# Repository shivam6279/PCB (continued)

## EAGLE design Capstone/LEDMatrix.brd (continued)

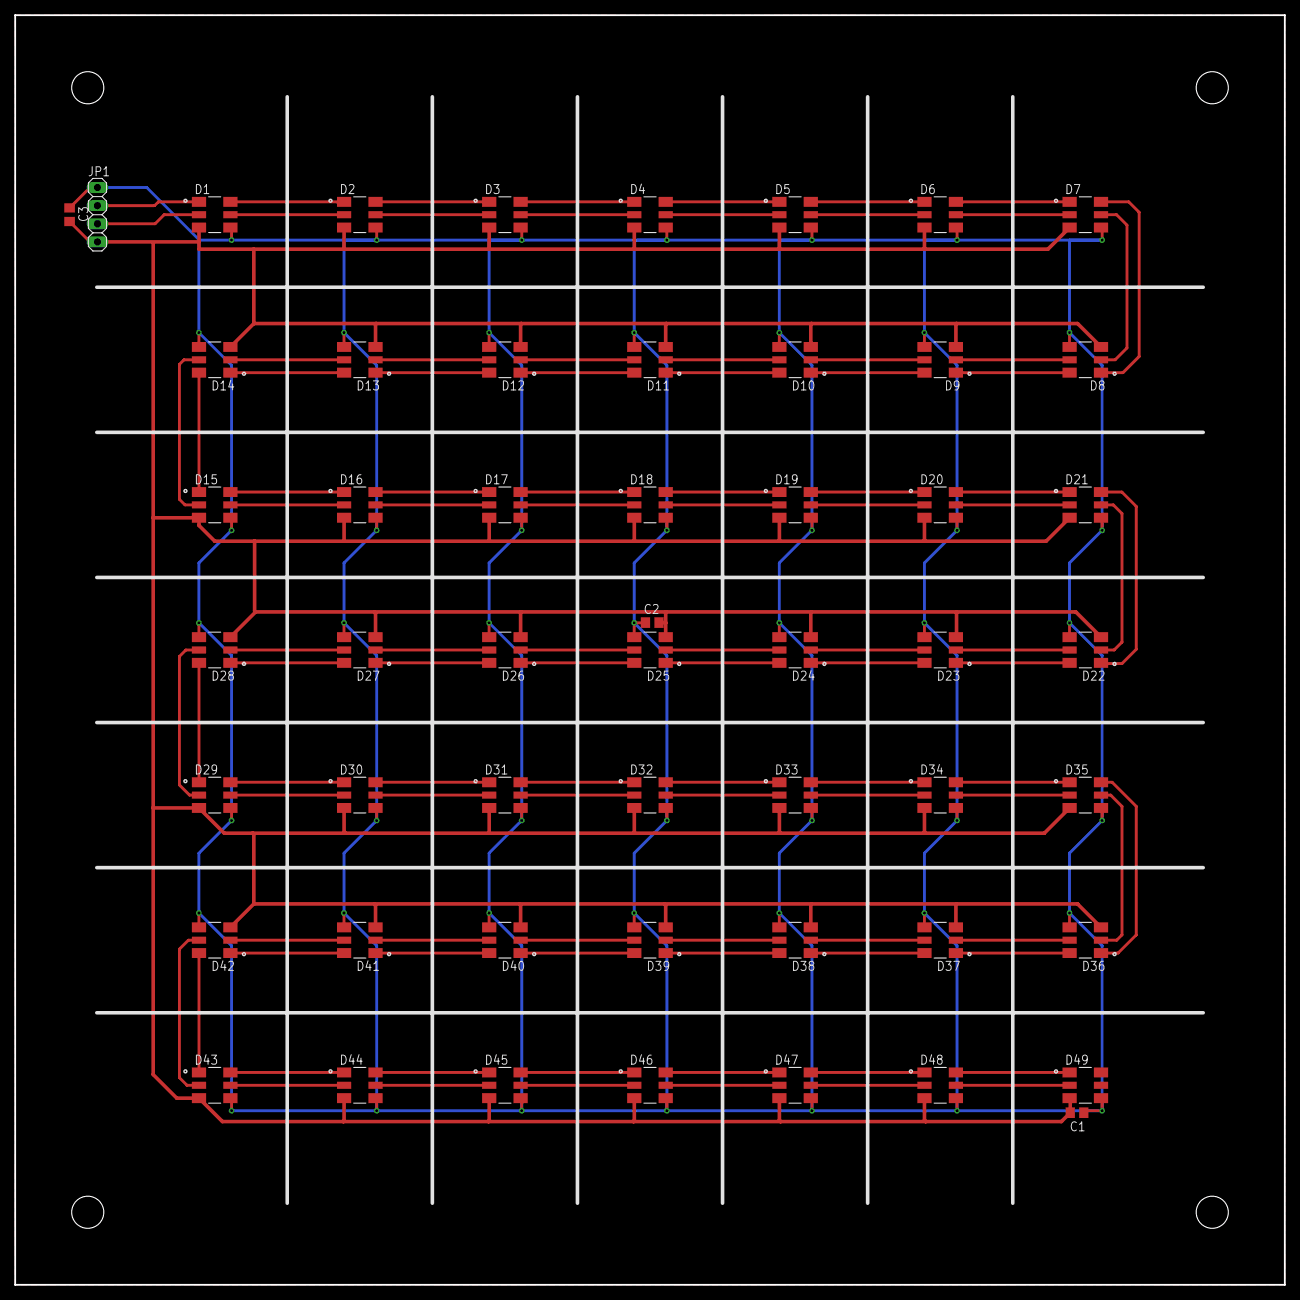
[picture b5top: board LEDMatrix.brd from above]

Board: 2 copper layers, 177.8 x 177.8 mm, 53 parts (0 on the bottom side), 100 nets.

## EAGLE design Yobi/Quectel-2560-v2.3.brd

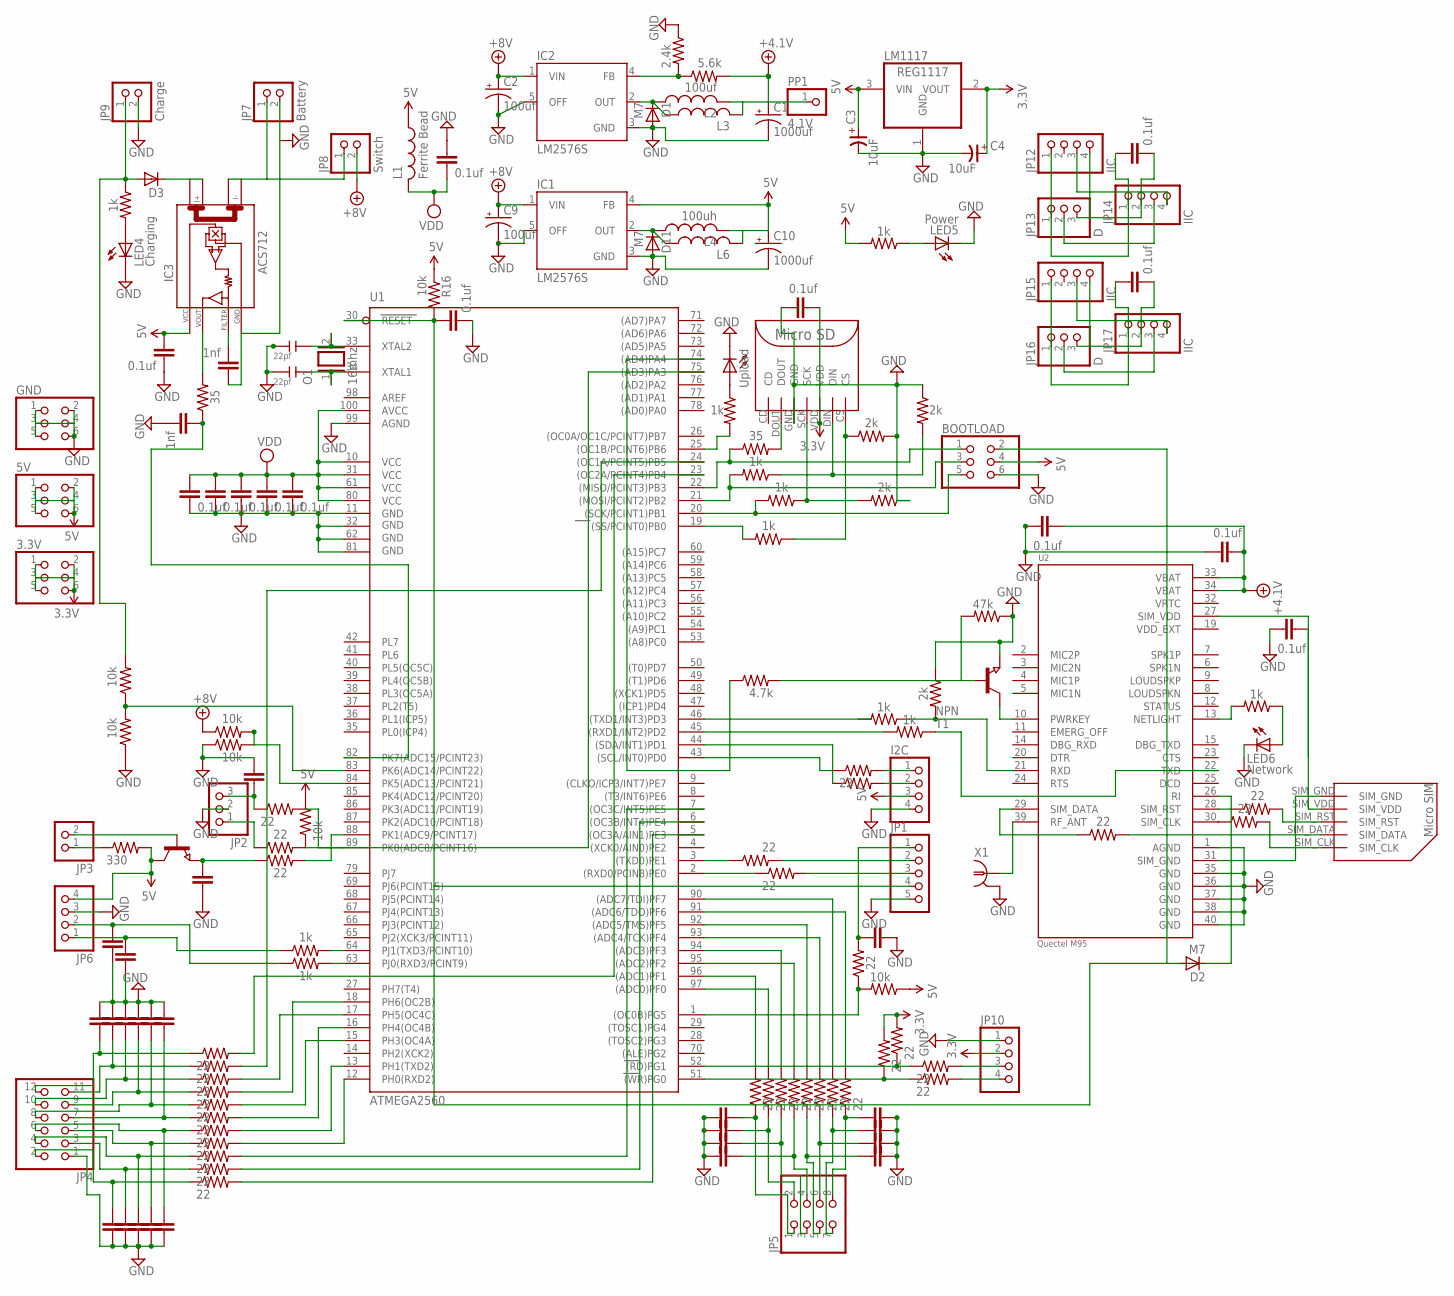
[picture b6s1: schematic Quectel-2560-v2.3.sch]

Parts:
3.3V, 5V: PINHD-2X3; 2X03
BOOTLOAD: PINHD-2X3; 2X03
C1, C10: 1000uf; 153CLV-1012
C2, C9: 100uf; CT7343
C3, C4: 10uF; 3528/T
C7, C8: 22pf; C0805
D1, D2, D11: M7; SOD106A
D3: BYS10; SOD106A
DC1, DC2, DC3, DC4, DC5, DC6, DC7, DC8, DC9, DC10, DC11, DC15, DC18, DC19: 0.1uf; C0805
DC12, DC13, DC14, DC16, DC17, DC20, DC21, DC22, DC23, DC24, DC25, DC26, DC27, DC28, DC29, DC30, DC31, DC32, DC33, DC34, DC35, DC36, DC37, DC38, DC39, DC40: 1nf; C0805
GND: PINHD-2X3; 2X03
I2C: PINHD-1X4; 1X04
IC1, IC2: LM2576S; TO263-5
IC3: ACS712; SO08
JP1: PINHD-1X5; 1X05
JP2: PINHD-1X3; 1X03
JP3: PINHD-1X2; 1X02
JP4: PINHD-2X6; 2X06
JP5: PINHD-2X4; 2X04
JP6, JP10: PINHD-1X4; 1X04
JP7: Battery; 1X02
JP8: Switch; 1X02
JP9: Charge; 1X02
JP12, JP14, JP15, JP17: IIC; 1X04
JP13, JP16: D; 1X03
L1: Ferrite Bead; L2012C
L2: 100uf; PIS2816
L3, L6: L-US6000-XXX-RC; 6000-XXXX-RC
L4: 100uh; PIS2816
LED2: Upload; CHIP-LED0805
LED4: Charging; CHIP-LED0805
LED5: Power; CHIP-LED0805
LED6: Network; CHIP-LED0805
LM1117: REG1117; SOT223
O1: 16mhz; QS
PP1: 4.1V; 1X01
R1, R35: 35; 0805
R2: 47k; 0805
R3: 4.7k; 0805
R4, R5, R12, R13, R19, R20, R21, R22, R27, R28, R30, R31, R32, R33, R34, R36, R37, R38, R39, R40, R41, R42, R48, R49, R51, R53, R54, R60, R61, R62, R63: 22; R0805
R6, R7, R8, R14, R15, R17, R18, R25, R26: 1k; 0805
R9, R23, R24, R29: 2k; 0805
R10, R11, R47: 22; 0805
R16, R43, R44, R56, R57: 10k; 0805
R45: 2.4k; 0805
R46: 5.6k; 0805
R50, R55: 10k; R0805
R52: 330; R0805
R58, R59: 1k; R0805
T1, T2: NPN; SOT23
U1: ATMEGA2560; TQFP100
U2: Quectel M95; XCVR_M95
U$1: MICROSD
U$2: MICROSIM
X1: LTI-SASF54GT

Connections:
3.3V: 3.3V.1, 3.3V.2, 3.3V.3, 3.3V.4, 3.3V.5, 3.3V.6, C4.+, DC10.2, JP10.2, LM1117.2 (VOUT), R62.2, R63.2, U$1.VDD
5V: 5V.1, 5V.2, 5V.3, 5V.4, 5V.5, 5V.6, BOOTLOAD.4, C3.+, C10.+, DC19.2, I2C.3, IC1.4 (FB), IC3.8 (VCC), JP6.4, L1.1, L4.2, L6.2, LM1117.3 (VIN), R16.1, R18.2, R50.1, R52.2, R55.2, T2.3 (C)
+4.1V: C1.+, DC6.2, DC7.2, L2.2, L3.2, PP1.1, R46.2, U2.33 (VBAT), U2.34 (VBAT)
+8V: C2.+, C9.+, IC1.1 (VIN), IC2.1 (VIN), JP8.2, R43.1
GND: BOOTLOAD.6, C1.-, C2.-, C3.-, C4.-, C7.1, C8.1, C9.-, C10.-, D1.A, D11.A, DC1.2, DC2.2, DC3.2, DC4.2, DC5.2, DC6.1, DC7.1, DC10.1, DC11.2, DC12.1, DC13.1, DC14.1, DC15.1, DC16.1, DC17.1, DC18.1, DC19.1, DC20.1, DC21.2, DC22.1, DC23.2, DC24.2, DC25.2, DC26.2, DC27.2, DC28.2, DC29.2, DC30.2, DC31.2, DC32.2, DC33.1, DC34.1, DC35.1, DC36.1, DC37.2, DC38.2, DC39.1, DC40.2, GND.1, GND.2, GND.3, GND.4, GND.5, GND.6, I2C.4, IC1.3 (GND), IC1.5 (OFF), IC2.3 (GND), IC2.5 (OFF), IC3.5 (GND), JP1.5, JP2.2, JP4.1, JP6.3, JP7.2, JP9.2, JP10.1, LED2.C, LED4.C, LED5.C, LED6.C, LM1117.1 (GND), R2.1, R9.1, R23.2, R24.1, R29.1, R44.1, R45.1, R57.1, T1.2 (E), U1.11 (GND), U1.32 (GND1), U1.62 (GND2), U1.81 (GND3), U1.99 (AGND), U2.1 (AGND), U2.35 (GND), U2.36 (GND), U2.37 (GND), U2.38 (GND), U2.40 (GND), U$1.GND, X1.2, X1.3 (2), X1.4 (2), X1.5 (2)
unnamed: U2.31 (SIM_GND), U$2.SIM_GND
unnamed: DC15.2, U2.27 (SIM_VDD), U$2.SIM_VDD
unnamed: R10.1, U2.28 (SIM_RST)
unnamed: R11.1, U2.30 (SIM_CLK)
unnamed: DC8.1, JP12.1, JP13.1, JP14.1
unnamed: R10.2, U$2.SIM_RST
unnamed: LED2.A, R25.1
unnamed: R33.1, R50.2, U1.1 ((OC0B)PG5)
unnamed: R32.2, U1.5 ((OC3A/AIN1)PE3)
unnamed: R7.1, R24.2, U$1.SCK
unnamed: R31.2, U1.6 ((OC3B/INT4)PE4)
unnamed: R6.1, R9.2, U$1.DIN
unnamed: BOOTLOAD.2, D2.A, DC11.1, JP1.4, R16.2, U1.30 (RESET)
unnamed: DC8.2, JP12.4, JP13.3, JP14.2
unnamed: JP13.2, JP14.3
unnamed: BOOTLOAD.3, R6.2, U1.21 ((MOSI/PCINT2)PB2)
unnamed: BOOTLOAD.5, R7.2, U1.20 ((SCK/PCINT1)PB1)
unnamed: DC21.1, R1.1, U1.82 (PK7(ADC15/PCINT23))
unnamed: IC3.4 (I-_1), JP7.1, JP8.1
unnamed: R8.2, U1.19 ((SS/PCINT0)PB0)
unnamed: U2.39 (RF_ANT), X1.1
unnamed: R13.2, U1.18 (PH6(OC2B))
unnamed: R22.2, U1.12 (PH0(RXD2))
unnamed: D3.A, JP9.1, R26.1, R56.2
unnamed: R27.2, U1.96 ((ADC1)PF1)
unnamed: LED4.A, R26.2
unnamed: IC3.7 (VOUT), R1.2
unnamed: R11.2, U$2.SIM_CLK
unnamed: C7.2, O1.2, U1.33 (XTAL2)
unnamed: C8.2, O1.1, U1.34 (XTAL1)
unnamed: R21.2, U1.13 (PH1(TXD2))
unnamed: R28.2, U1.97 ((ADC0)PF0)
unnamed: R34.2, U1.94 ((ADC3)PF3)
unnamed: R8.1, R23.1, U$1.CS
unnamed: R19.2, U1.15 (PH3(OC4A))
unnamed: R20.2, U1.16 (PH4(OC4B))
unnamed: R12.2, U1.17 (PH5(OC4C))
unnamed: R25.2, U1.25 ((OC1B/PCINT6)PB6)
unnamed: R14.2, U1.46 ((TXD1/INT3)PD3)
unnamed: R15.2, U1.45 ((RXD1/INT2)PD2)
unnamed: R14.1, R29.2, U2.21 (RXD)
unnamed: R15.1, U2.22 (TXD)
unnamed: DC29.1, JP5.8, R40.1
unnamed: R4.2, U1.23 ((OC2A/PCINT4)PB4)
unnamed: JP12.3, JP14.4
unnamed: R5.2, U1.24 ((OC1A/PCINT5)PB5)
unnamed: R36.2, U1.95 ((ADC2)PF2)
unnamed: BOOTLOAD.1, R35.1, U1.22 ((MISO/PCINT3)PB3)
unnamed: R17.2, U2.13 (NETLIGHT)
unnamed: LED6.A, R17.1
unnamed: R41.1, U1.3 ((TXD0)PE1)
unnamed: R42.1, U1.2 ((RXD0/PCIN8)PE0)
unnamed: DC13.2, JP4.11, R5.1
unnamed: DC23.1, JP1.1, R33.2
unnamed: DC25.1, JP4.3, R31.1
unnamed: DC27.1, JP4.5, R22.1
unnamed: DC22.2, JP4.7, R20.1
unnamed: LED5.A, R18.1
unnamed: DC16.2, JP4.9, R13.1
unnamed: DC24.1, JP4.2, R32.1
unnamed: JP1.2, R41.2
unnamed: R35.2, U$1.DOUT
unnamed: D11.K, IC1.2 (OUT), L4.1, L6.1
unnamed: DC28.1, JP4.6, R21.1
unnamed: R47.2, U$2.SIM_DATA
unnamed: R47.1, U2.29 (SIM_DATA)
unnamed: DC17.2, JP4.8, R19.1
unnamed: DC14.2, JP4.10, R12.1
unnamed: DC12.2, JP4.12, R4.1
unnamed: DC9.1, JP15.1, JP16.1, JP17.1
unnamed: DC26.1, JP4.4, R30.1
unnamed: JP1.3, R42.2
unnamed: R30.2, U1.7 ((OC3C/INT5)PE5)
unnamed: R43.2, R44.2, U1.84 (PK5(ADC13/PCINT21))
unnamed: D1.K, IC2.2 (OUT), L2.1, L3.1
unnamed: IC2.4 (FB), R45.2, R46.1
unnamed: DC39.2, JP2.3, R51.1
unnamed: I2C.1, R49.2
unnamed: I2C.2, R48.2
unnamed: DC9.2, JP15.4, JP16.3, JP17.2
unnamed: JP15.3, JP17.4
unnamed: JP16.2, JP17.3
unnamed: T1.3 (C), U2.10 (PWRKEY)
unnamed: R2.2, R3.2, T1.1 (B)
unnamed: R3.1, U1.74 ((AD4)PA4)
unnamed: D2.K, U2.26 (RI)
unnamed: DC31.1, JP5.6, R37.1
unnamed: D3.K, IC3.1 (I+_0)
unnamed: DC20.2, IC3.6 (FILTER)
unnamed: DC36.2, JP5.4, R36.1
unnamed: DC34.2, JP5.2, R28.1
unnamed: R48.1, U1.44 ((SDA/INT1)PD1)
unnamed: R49.1, U1.43 ((SCL/INT0)PD0)
unnamed: DC30.1, JP5.7, R39.1
unnamed: DC32.1, JP5.5, R38.1
unnamed: DC35.2, JP5.3, R34.1
unnamed: DC33.2, JP5.1, R27.1
unnamed: R38.2, U1.92 ((ADC5/TMS)PF5)
unnamed: R37.2, U1.93 ((ADC4/TCK)PF4)
unnamed: R39.2, U1.90 ((ADC7/TDI)PF7)
unnamed: R40.2, U1.91 ((ADC6/TDO)PF6)
unnamed: JP2.1, R54.1
unnamed: JP3.1, R52.1
unnamed: JP3.2, T2.1 (B)
unnamed: DC40.1, R53.1, T2.2 (E)
unnamed: R54.2, R55.1, U1.75 ((AD3)PA3)
unnamed: R51.2, U1.89 (PK0(ADC8/PCINT16))
unnamed: R53.2, U1.88 (PK1(ADC9/PCINT17))
unnamed: R60.1, R62.1, U1.51 ((WR)PG0)
unnamed: R56.1, R57.2, U1.83 (PK6(ADC14/PCINT22))
unnamed: R58.2, U1.64 (PJ1(TXD3/PCINT10))
unnamed: R59.2, U1.63 (PJ0(RXD3/PCINT9))
unnamed: DC38.1, JP6.1, R58.1
unnamed: DC37.1, JP6.2, R59.1
unnamed: R61.1, R63.1, U1.52 ((RD)PG1)
unnamed: JP10.4, R60.2
unnamed: JP10.3, R61.2
VDD: DC1.1, DC2.1, DC3.1, DC4.1, DC5.1, DC18.2, L1.2, U1.10 (VCC), U1.31 (VCC1), U1.61 (VCC2), U1.80 (VCC3), U1.100 (AVCC)
VDD_EXT: U2.19 (VDD_EXT)
VRTC: U2.32 (VRTC)

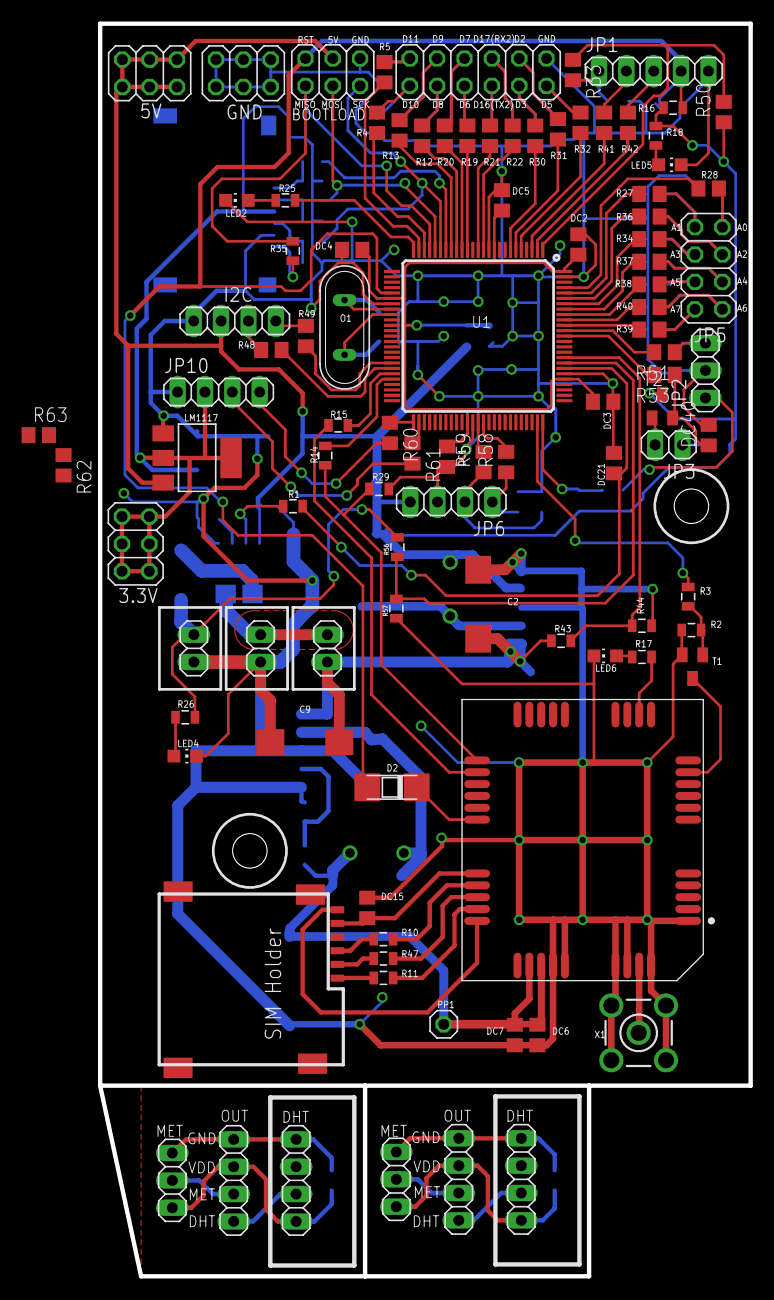
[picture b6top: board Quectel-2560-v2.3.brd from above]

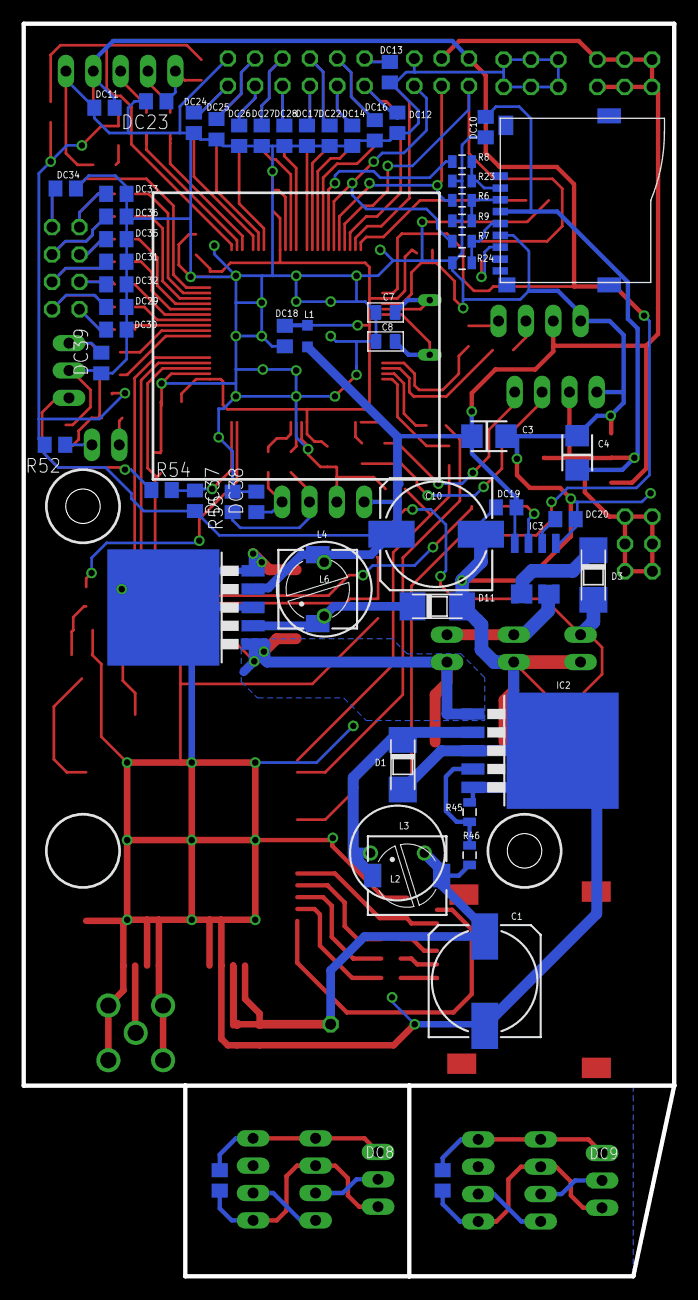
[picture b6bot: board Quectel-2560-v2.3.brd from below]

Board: 2 copper layers, 60.4 x 116.3 mm, 158 parts (59 on the bottom side), 123 nets.

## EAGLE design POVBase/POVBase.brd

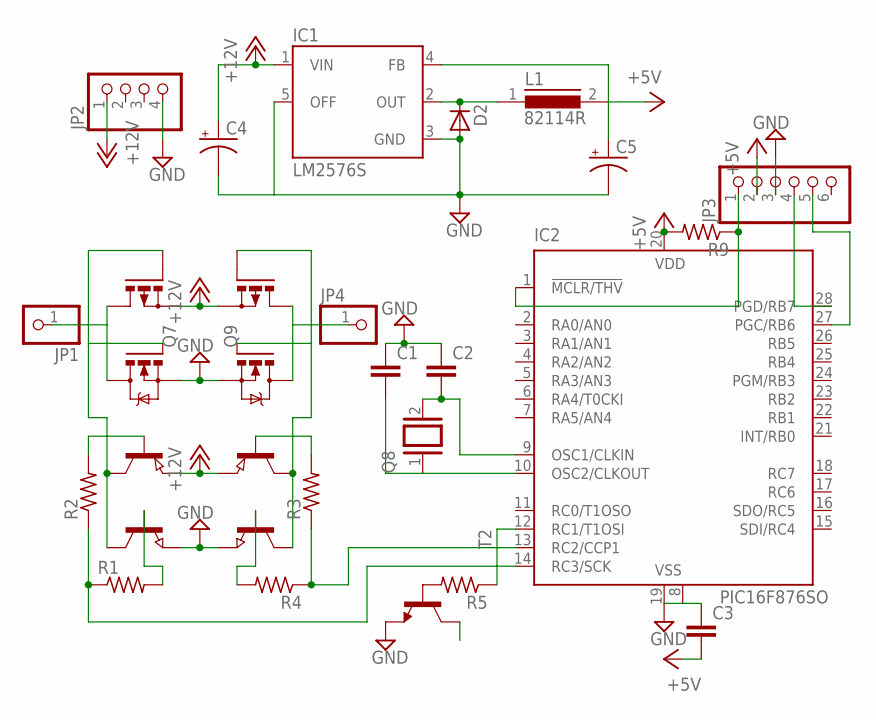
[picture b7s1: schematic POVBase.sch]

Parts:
C1, C2, C3: C-EUC0805; C0805
C4: CPOL-USE2.5-7; E2,5-7
C5: CPOL-USE1.8-4; E1,8-4
D2: DIODE_E-SMC; DIODE_SMC
IC1: LM2576S; TO263-5
IC2: PIC16F876SO; SO28W
JP1, JP4: PINHD-1X1; 1X01
JP2: PINHD-1X4; 1X04
JP3: PINHD-1X6; 1X06
L1: 82114R
Q1, Q2: NPN-TRANSISTOR_SOT23; SOT23
Q3, Q4: PNP-TRANSISTOR_SOT23; SOT23
Q5, Q6: IRF540; TO220BV
Q7, Q9: PMOSFET_PTO220BV; TO220BV
Q8: XTAL/S; QS
R1, R2, R3, R4, R5, R9: R-US_R0805; R0805
T2: 2SC1306; TO220BV

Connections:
+5V: C3.2, C5.+, IC1.4 (FB), IC2.20 (VDD), JP3.2, L1.2, R9.2
+12V: C4.+, IC1.1 (VIN), JP2.1, Q3.2 (E), Q4.2 (E), Q7.S, Q9.S
GND: C1.1, C2.1, C3.1, C4.-, C5.-, D2.A (C), IC1.3 (GND), IC1.5 (OFF), IC2.8 (VSS), IC2.19 (VSS), JP2.4, JP3.3, Q1.2 (E), Q2.2 (E), Q5.S, Q6.S, T2.3 (E)
unnamed: Q1.3 (C), Q3.3 (C), Q5.G, Q7.G
unnamed: Q1.1 (B), R1.2
unnamed: Q2.1 (B), R4.2
unnamed: Q2.3 (C), Q4.3 (C), Q6.G, Q9.G
unnamed: Q3.1 (B), R2.2
unnamed: Q4.1 (B), R3.2
unnamed: IC2.14 (RC3/SCK), R1.1, R2.1
unnamed: IC2.13 (RC2/CCP1), R3.1, R4.1
unnamed: JP4.1, Q6.D, Q9.D
unnamed: JP1.1, Q5.D, Q7.D
unnamed: IC2.1 (!MCLR/THV), JP3.1, R9.1
unnamed: IC2.28 (PGD/RB7), JP3.4
unnamed: IC2.27 (PGC/RB6), JP3.5
unnamed: D2.C (A), IC1.2 (OUT), L1.1
unnamed: C1.2, IC2.10 (OSC2/CLKOUT), Q8.1
unnamed: C2.2, IC2.9 (OSC1/CLKIN), Q8.2
unnamed: IC2.12 (RC1/T1OSI), R5.1
unnamed: R5.2, T2.1 (B)

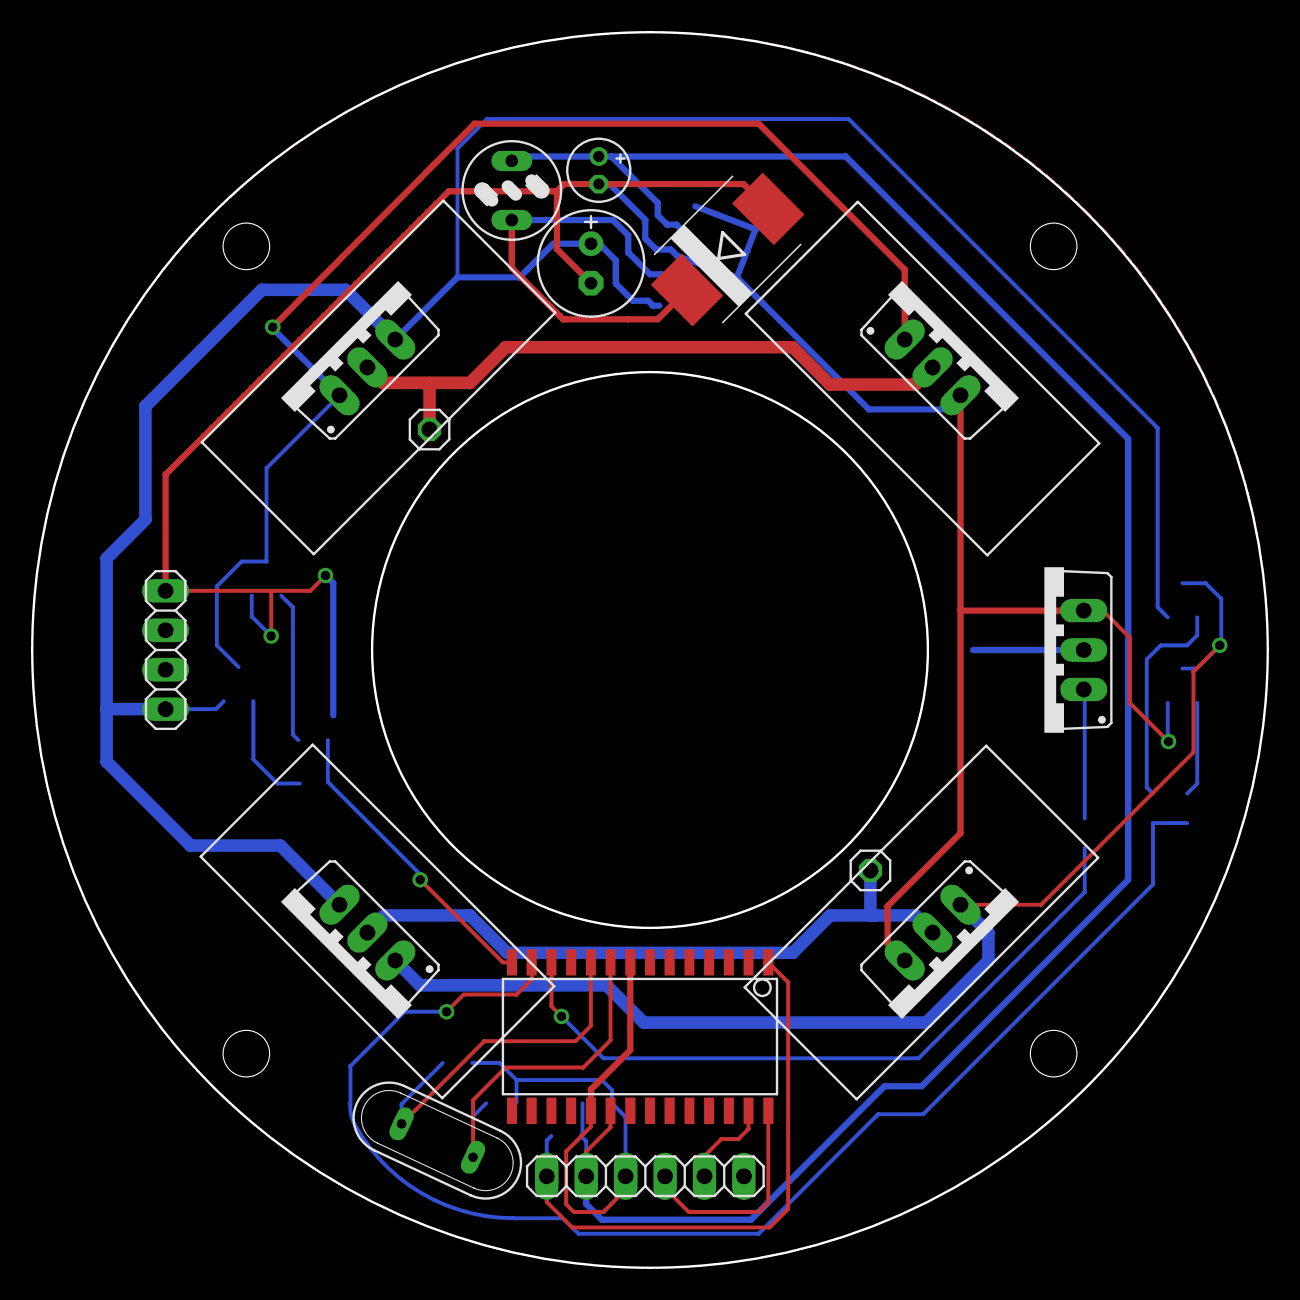
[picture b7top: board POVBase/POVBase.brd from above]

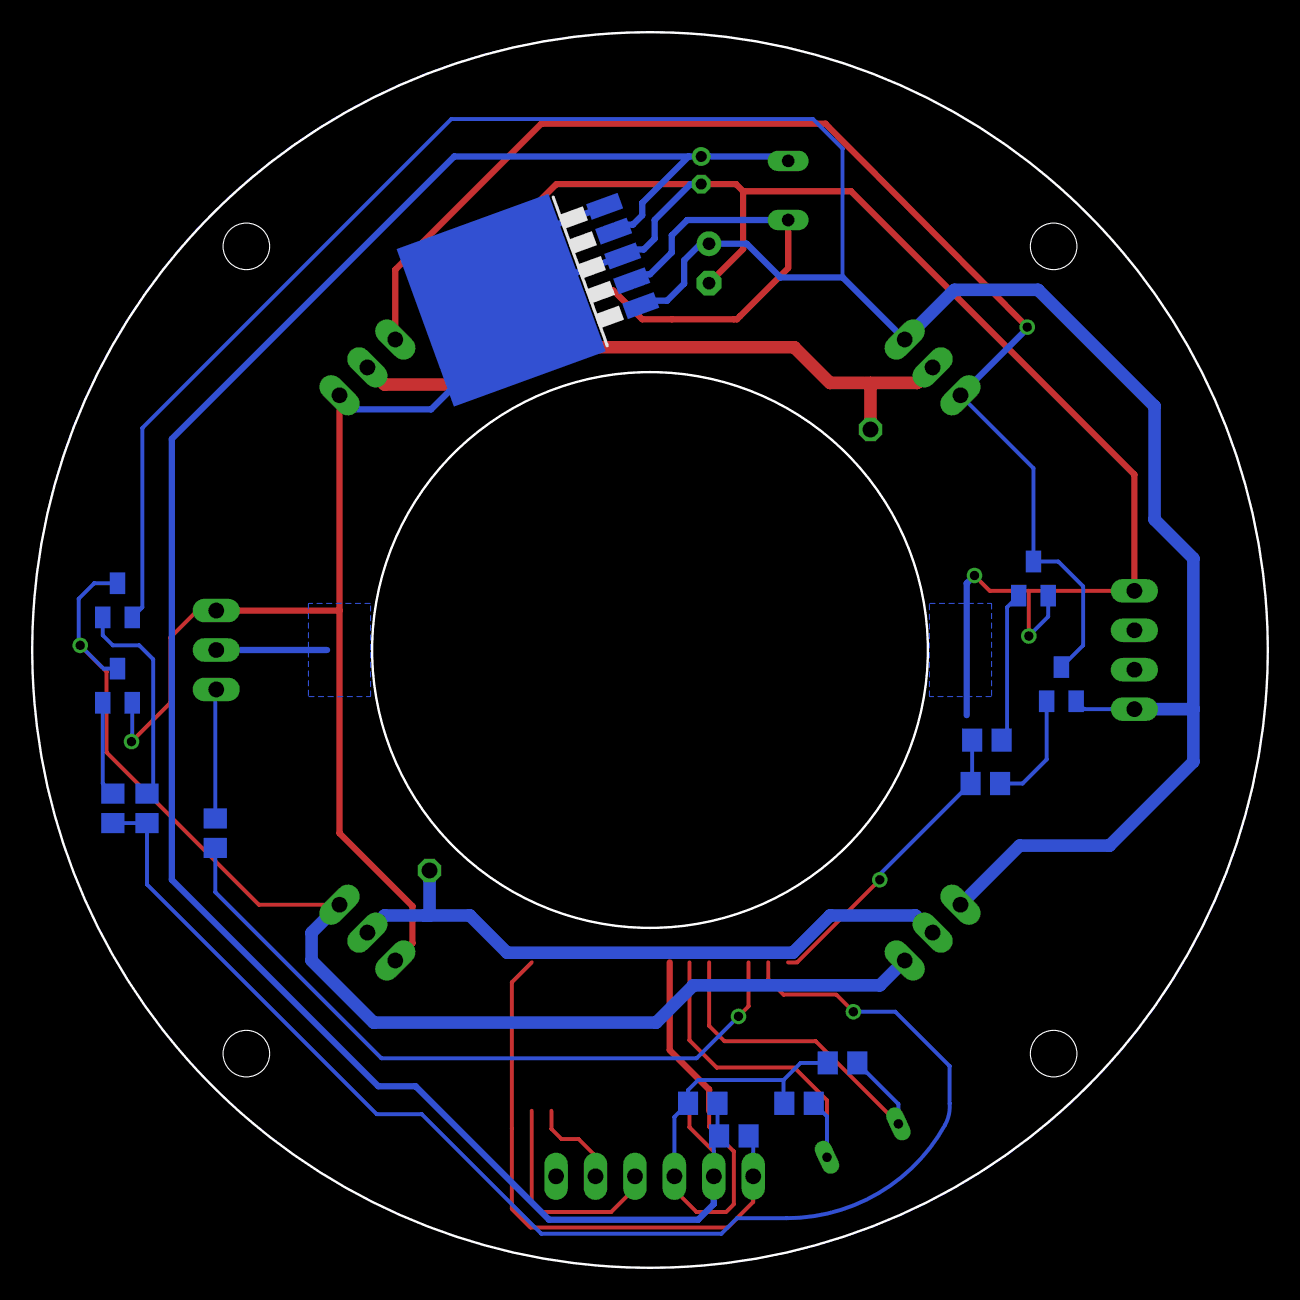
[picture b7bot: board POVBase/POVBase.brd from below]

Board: 2 copper layers, 79.6 x 79.6 mm, 29 parts (14 on the bottom side), 21 nets.

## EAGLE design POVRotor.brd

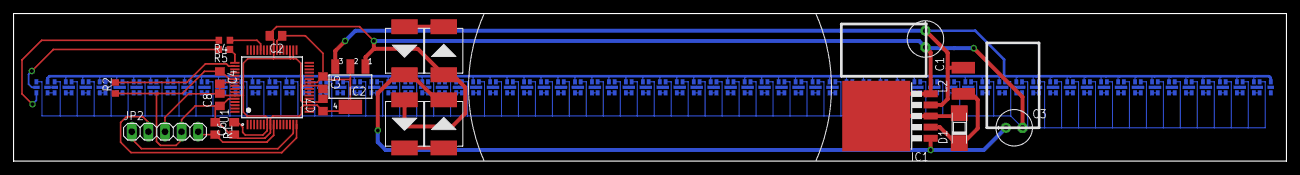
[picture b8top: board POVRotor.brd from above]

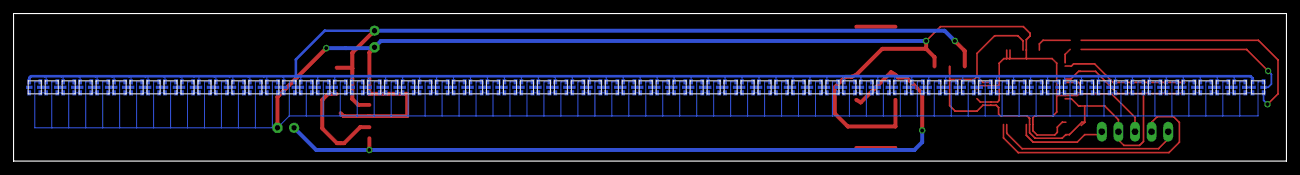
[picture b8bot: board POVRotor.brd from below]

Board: 2 copper layers, 195.0 x 22.6 mm, 95 parts (73 on the bottom side), 159 nets.

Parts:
C1, C3: E2,5-6E
C2, C4, C5, C6, C7, C8: C0805
D1: SOD106A
D2, D3, D4, D5: SMD-DIODE-SCHOTTKY-40V-3A(DO-214AB); DO-214AB
IC1: LM2576S; TO263-5
IC2: SOT223
JP2: 1X05
L2: L4532P
R1: R0805
R2, R4, R5: R0603
U1: PIC32MZ2048EFH064-I/PT; QFP50P1200X1200X120-64N
U$1, U$2, U$3, U$4, U$5, U$6, U$7, U$8, U$9, U$10, U$11, U$12, U$13, U$14, U$15, U$16, U$17, U$18, U$19, U$20, U$21, U$22, U$23, U$24, U$25, U$26, U$27, U$28, U$29, U$30, U$31, U$32, U$33, U$34, U$35, U$36, U$37, U$38, U$39, U$40, U$41, U$42, U$43, U$44, U$45, U$46, U$47, U$48, U$49, U$50, U$51, U$52, U$53, U$54, U$55, U$56, U$57, U$58, U$59, U$60, U$61, U$62, U$63, U$64, U$65, U$66, U$67, U$68, U$69, U$70, U$71, U$72, U$73: 2020LED

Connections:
+3V3: C2.1, C4.1, C5.1, C6.1, C7.1, C8.1, IC2.2, JP2.4, R1.1, R2.1, U1.8, U1.19, U1.26, U1.39, U1.54, U1.60
+5V: C1.+, IC1.4, IC2.3, L2.2, U$1.VCC, U$2.VCC, U$3.VCC, U$4.VCC, U$5.VCC, U$6.VCC, U$7.VCC, U$8.VCC, U$9.VCC, U$10.VCC, U$11.VCC, U$12.VCC, U$13.VCC, U$14.VCC, U$15.VCC, U$16.VCC, U$17.VCC, U$18.VCC, U$19.VCC, U$20.VCC, U$21.VCC, U$22.VCC, U$23.VCC, U$24.VCC, U$25.VCC, U$26.VCC, U$27.VCC, U$28.VCC, U$29.VCC, U$30.VCC, U$31.VCC, U$32.VCC, U$33.VCC, U$34.VCC, U$35.VCC, U$36.VCC, U$37.VCC, U$38.VCC, U$39.VCC, U$40.VCC, U$41.VCC, U$42.VCC, U$43.VCC, U$44.VCC, U$45.VCC, U$46.VCC, U$47.VCC, U$48.VCC, U$49.VCC, U$50.VCC, U$51.VCC, U$52.VCC, U$53.VCC, U$54.VCC, U$55.VCC, U$56.VCC, U$57.VCC, U$58.VCC, U$59.VCC, U$60.VCC, U$61.VCC, U$62.VCC, U$63.VCC, U$64.VCC, U$65.VCC, U$66.VCC, U$67.VCC, U$68.VCC, U$69.VCC, U$70.VCC, U$71.VCC, U$72.VCC, U$73.VCC
+15V: C3.+, D2.2, D3.2, IC1.1
GND: C1.-, C2.2, C3.-, C4.2, C5.2, C6.2, C7.2, C8.2, D1.A, D4.1, D5.1, IC1.3, IC1.5, IC2.1, JP2.3, U1.7, U1.20, U1.25, U1.34, U1.35, U1.40, U1.55, U1.59, U$1.GND, U$2.GND, U$3.GND, U$4.GND, U$5.GND, U$6.GND, U$7.GND, U$8.GND, U$9.GND, U$10.GND, U$11.GND, U$12.GND, U$13.GND, U$14.GND, U$15.GND, U$16.GND, U$17.GND, U$18.GND, U$19.GND, U$20.GND, U$21.GND, U$22.GND, U$23.GND, U$24.GND, U$25.GND, U$26.GND, U$27.GND, U$28.GND, U$29.GND, U$30.GND, U$31.GND, U$32.GND, U$33.GND, U$34.GND, U$35.GND, U$36.GND, U$37.GND, U$38.GND, U$39.GND, U$40.GND, U$41.GND, U$42.GND, U$43.GND, U$44.GND, U$45.GND, U$46.GND, U$47.GND, U$48.GND, U$49.GND, U$50.GND, U$51.GND, U$52.GND, U$53.GND, U$54.GND, U$55.GND, U$56.GND, U$57.GND, U$58.GND, U$59.GND, U$60.GND, U$61.GND, U$62.GND, U$63.GND, U$64.GND, U$65.GND, U$66.GND, U$67.GND, U$68.GND, U$69.GND, U$70.GND, U$71.GND, U$72.GND, U$73.GND
unnamed: D2.1, D5.2
unnamed: D3.1, D4.2
unnamed: D1.K, IC1.2, L2.1
unnamed: R2.2, U1.50
unnamed: U$1.SDI, U$2.SDO
unnamed: U$10.SDO, U$11.SDI
unnamed: U$10.CLKO, U$11.CLKI
unnamed: U$1.CLKI, U$2.CLKO
unnamed: U$11.SDO, U$12.SDI
unnamed: JP2.2, U1.16
unnamed: JP2.1, U1.15
unnamed: JP2.5, R1.2, U1.9
unnamed: R4.2, U$2.SDI
unnamed: U$1.SDO, U$3.SDI
unnamed: R5.2, U$2.CLKI
unnamed: R5.1, U1.49
unnamed: U$1.CLKO, U$3.CLKI
unnamed: R4.1, U1.44
unnamed: U$11.CLKO, U$12.CLKI
unnamed: U$12.SDO, U$13.SDI
unnamed: U$12.CLKO, U$13.CLKI
unnamed: U$13.SDO, U$14.SDI
unnamed: U$3.SDO, U$4.SDI
unnamed: U$3.CLKO, U$4.CLKI
unnamed: U$13.CLKO, U$14.CLKI
unnamed: U$14.SDO, U$15.SDI
unnamed: U$14.CLKO, U$15.CLKI
unnamed: U$4.SDO, U$5.SDI
unnamed: U$4.CLKO, U$5.CLKI
unnamed: U$15.SDO, U$16.SDI
unnamed: U$15.CLKO, U$16.CLKI
unnamed: U$16.SDO, U$17.SDI
unnamed: U$16.CLKO, U$17.CLKI
unnamed: U$5.SDO, U$6.SDI
unnamed: U$5.CLKO, U$6.CLKI
unnamed: U$17.SDO, U$18.SDI
unnamed: U$17.CLKO, U$18.CLKI
unnamed: U$18.SDO, U$19.SDI
unnamed: U$18.CLKO, U$19.CLKI
unnamed: U$6.SDO, U$7.SDI
unnamed: U$19.SDO, U$20.SDI
unnamed: U$19.CLKO, U$20.CLKI
unnamed: U$20.SDO, U$21.SDI
unnamed: U$20.CLKO, U$21.CLKI
unnamed: U$21.SDO, U$22.SDI
unnamed: U$6.CLKO, U$7.CLKI
unnamed: U$21.CLKO, U$22.CLKI
unnamed: U$22.SDO, U$23.SDI
unnamed: U$22.CLKO, U$23.CLKI
unnamed: U$23.SDO, U$24.SDI
unnamed: U$23.CLKO, U$24.CLKI
unnamed: U$7.SDO, U$8.SDI
unnamed: U$24.SDO, U$25.SDI
unnamed: U$7.CLKO, U$8.CLKI
unnamed: U$24.CLKO, U$25.CLKI
unnamed: U$25.SDO, U$26.SDI
unnamed: U$25.CLKO, U$26.CLKI
unnamed: U$8.SDO, U$9.SDI
unnamed: U$8.CLKO, U$9.CLKI
unnamed: U$26.SDO, U$27.SDI
unnamed: U$26.CLKO, U$27.CLKI
unnamed: U$9.SDO, U$10.SDI
unnamed: U$9.CLKO, U$10.CLKI
unnamed: U$27.SDO, U$28.SDI
unnamed: U$27.CLKO, U$28.CLKI
unnamed: U$28.SDO, U$29.SDI
unnamed: U$28.CLKO, U$29.CLKI
unnamed: U$29.SDO, U$30.SDI
unnamed: U$29.CLKO, U$30.CLKI
unnamed: U$30.SDO, U$31.SDI
unnamed: U$30.CLKO, U$31.CLKI
unnamed: U$31.SDO, U$32.SDI
unnamed: U$31.CLKO, U$32.CLKI
unnamed: U$32.SDO, U$33.SDI
unnamed: U$32.CLKO, U$33.CLKI
unnamed: U$33.SDO, U$34.SDI
unnamed: U$33.CLKO, U$34.CLKI
unnamed: U$34.SDO, U$35.SDI
unnamed: U$34.CLKO, U$35.CLKI
unnamed: U$35.SDO, U$36.SDI
unnamed: U$35.CLKO, U$36.CLKI
unnamed: U$36.SDO, U$37.SDI
unnamed: U$36.CLKO, U$37.CLKI
unnamed: U$37.SDO, U$38.SDI
unnamed: U$37.CLKO, U$38.CLKI
unnamed: U$38.SDO, U$39.SDI
unnamed: U$38.CLKO, U$39.CLKI
unnamed: U$39.SDO, U$40.SDI
unnamed: U$39.CLKO, U$40.CLKI
unnamed: U$40.SDO, U$41.SDI
unnamed: U$40.CLKO, U$41.CLKI
unnamed: U$41.SDO, U$42.SDI
unnamed: U$41.CLKO, U$42.CLKI
unnamed: U$42.SDO, U$43.SDI
unnamed: U$42.CLKO, U$43.CLKI
unnamed: U$43.SDO, U$44.SDI
unnamed: U$43.CLKO, U$44.CLKI
unnamed: U$44.SDO, U$45.SDI
unnamed: U$44.CLKO, U$45.CLKI
unnamed: U$45.SDO, U$46.SDI
unnamed: U$45.CLKO, U$46.CLKI
unnamed: U$46.SDO, U$47.SDI
unnamed: U$46.CLKO, U$47.CLKI
unnamed: U$47.SDO, U$48.SDI
unnamed: U$47.CLKO, U$48.CLKI
unnamed: U$48.SDO, U$49.SDI
unnamed: U$48.CLKO, U$49.CLKI
unnamed: U$49.SDO, U$50.SDI
unnamed: U$49.CLKO, U$50.CLKI
unnamed: U$50.SDO, U$51.SDI
unnamed: U$50.CLKO, U$51.CLKI
unnamed: U$51.SDO, U$52.SDI
unnamed: U$51.CLKO, U$52.CLKI
unnamed: U$52.SDO, U$53.SDI
unnamed: U$52.CLKO, U$53.CLKI
unnamed: U$53.SDO, U$54.SDI
unnamed: U$53.CLKO, U$54.CLKI
unnamed: U$54.SDO, U$55.SDI
unnamed: U$54.CLKO, U$55.CLKI
unnamed: U$55.SDO, U$56.SDI
unnamed: U$55.CLKO, U$56.CLKI
unnamed: U$56.SDO, U$57.SDI
unnamed: U$56.CLKO, U$57.CLKI
unnamed: U$57.SDO, U$58.SDI
unnamed: U$57.CLKO, U$58.CLKI
unnamed: U$58.SDO, U$59.SDI
unnamed: U$58.CLKO, U$59.CLKI
unnamed: U$59.SDO, U$60.SDI
unnamed: U$59.CLKO, U$60.CLKI
unnamed: U$60.SDO, U$61.SDI
unnamed: U$60.CLKO, U$61.CLKI
unnamed: U$61.SDO, U$62.SDI
unnamed: U$61.CLKO, U$62.CLKI
unnamed: U$62.SDO, U$63.SDI
unnamed: U$62.CLKO, U$63.CLKI
unnamed: U$63.SDO, U$64.SDI
unnamed: U$63.CLKO, U$64.CLKI
unnamed: U$64.SDO, U$65.SDI
unnamed: U$64.CLKO, U$65.CLKI
unnamed: U$65.SDO, U$66.SDI
unnamed: U$65.CLKO, U$66.CLKI
unnamed: U$66.SDO, U$67.SDI
unnamed: U$66.CLKO, U$67.CLKI
unnamed: U$67.SDO, U$68.SDI
unnamed: U$67.CLKO, U$68.CLKI
unnamed: U$68.SDO, U$69.SDI
unnamed: U$68.CLKO, U$69.CLKI
unnamed: U$69.SDO, U$70.SDI
unnamed: U$69.CLKO, U$70.CLKI
unnamed: U$70.SDO, U$71.SDI
unnamed: U$70.CLKO, U$71.CLKI
unnamed: U$71.SDO, U$72.SDI
unnamed: U$71.CLKO, U$72.CLKI
unnamed: U$72.SDO, U$73.SDI
unnamed: U$72.CLKO, U$73.CLKI

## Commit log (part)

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2017-07-20 cbdg
2017-08-01 dfbfd
2017-08-01 xgns
2017-08-03 sdgs
2017-08-05 gfjfgj
2017-09-09 fhgjk
2017-11-04 hgkjhgk
2018-01-31 vfhjf
2018-03-07 cvbn
2020-08-16 Altium
2025-01-10 Moving general purpose ESCs from Cubli/motorboard to ESC
2025-01-11 Remove old gitignored files
